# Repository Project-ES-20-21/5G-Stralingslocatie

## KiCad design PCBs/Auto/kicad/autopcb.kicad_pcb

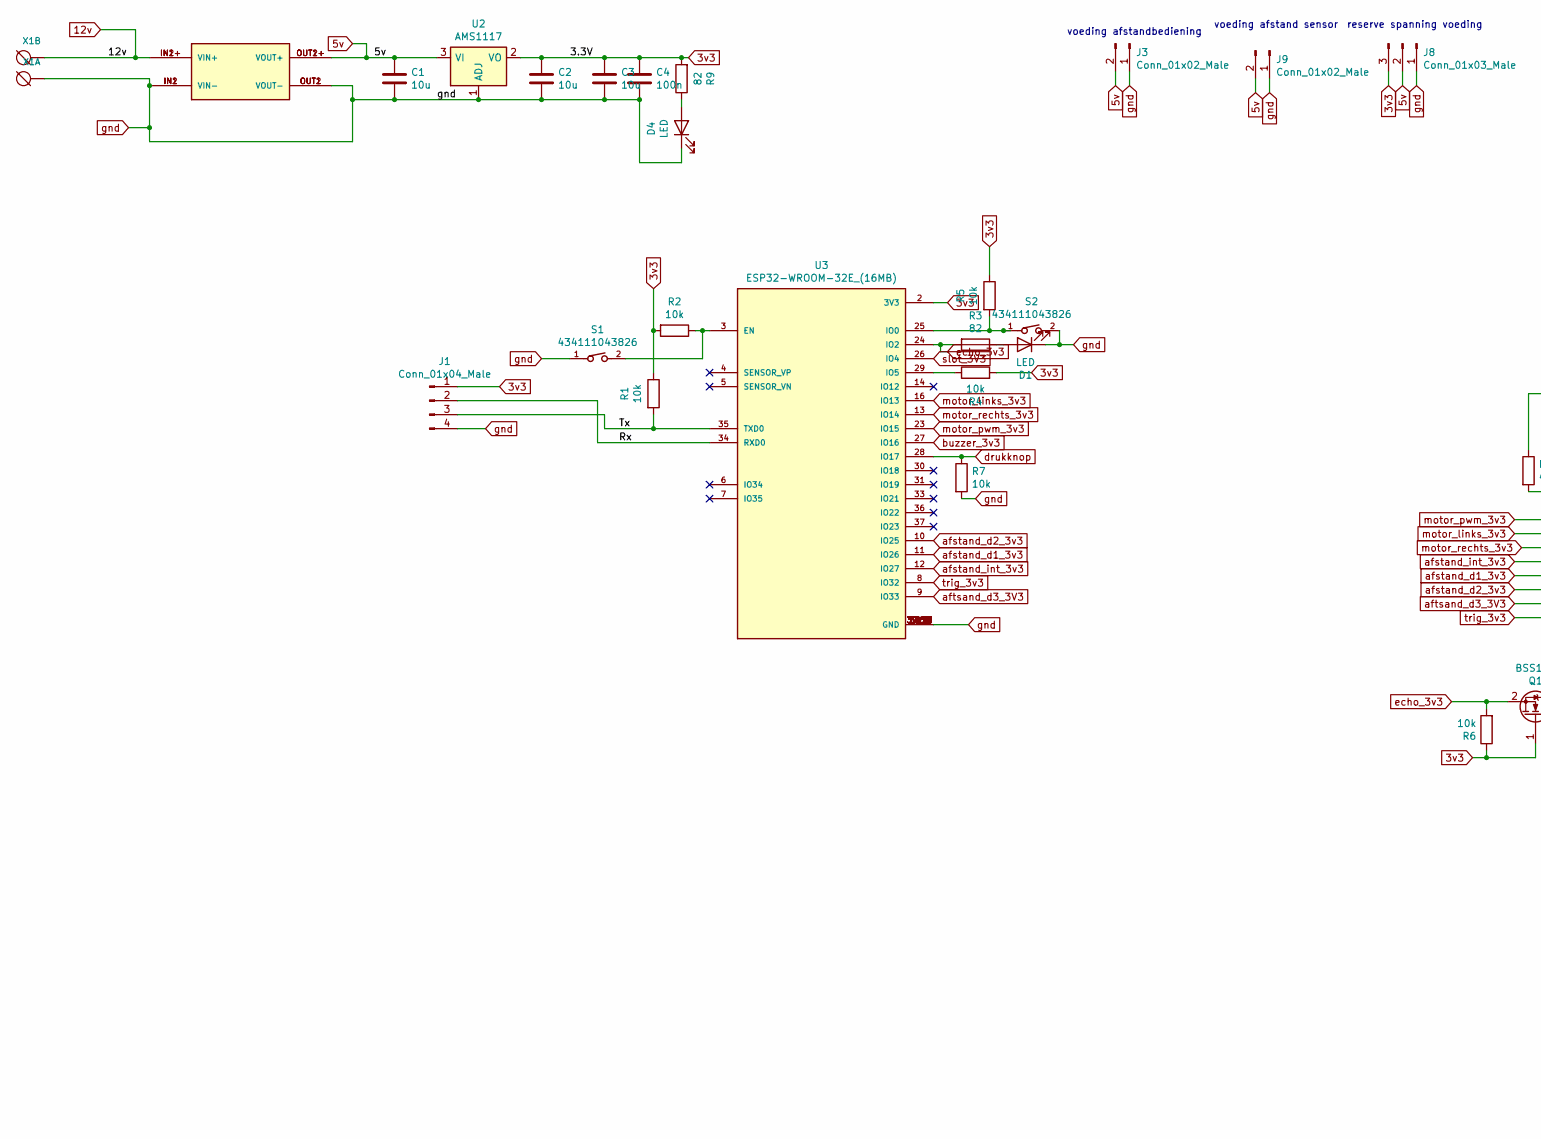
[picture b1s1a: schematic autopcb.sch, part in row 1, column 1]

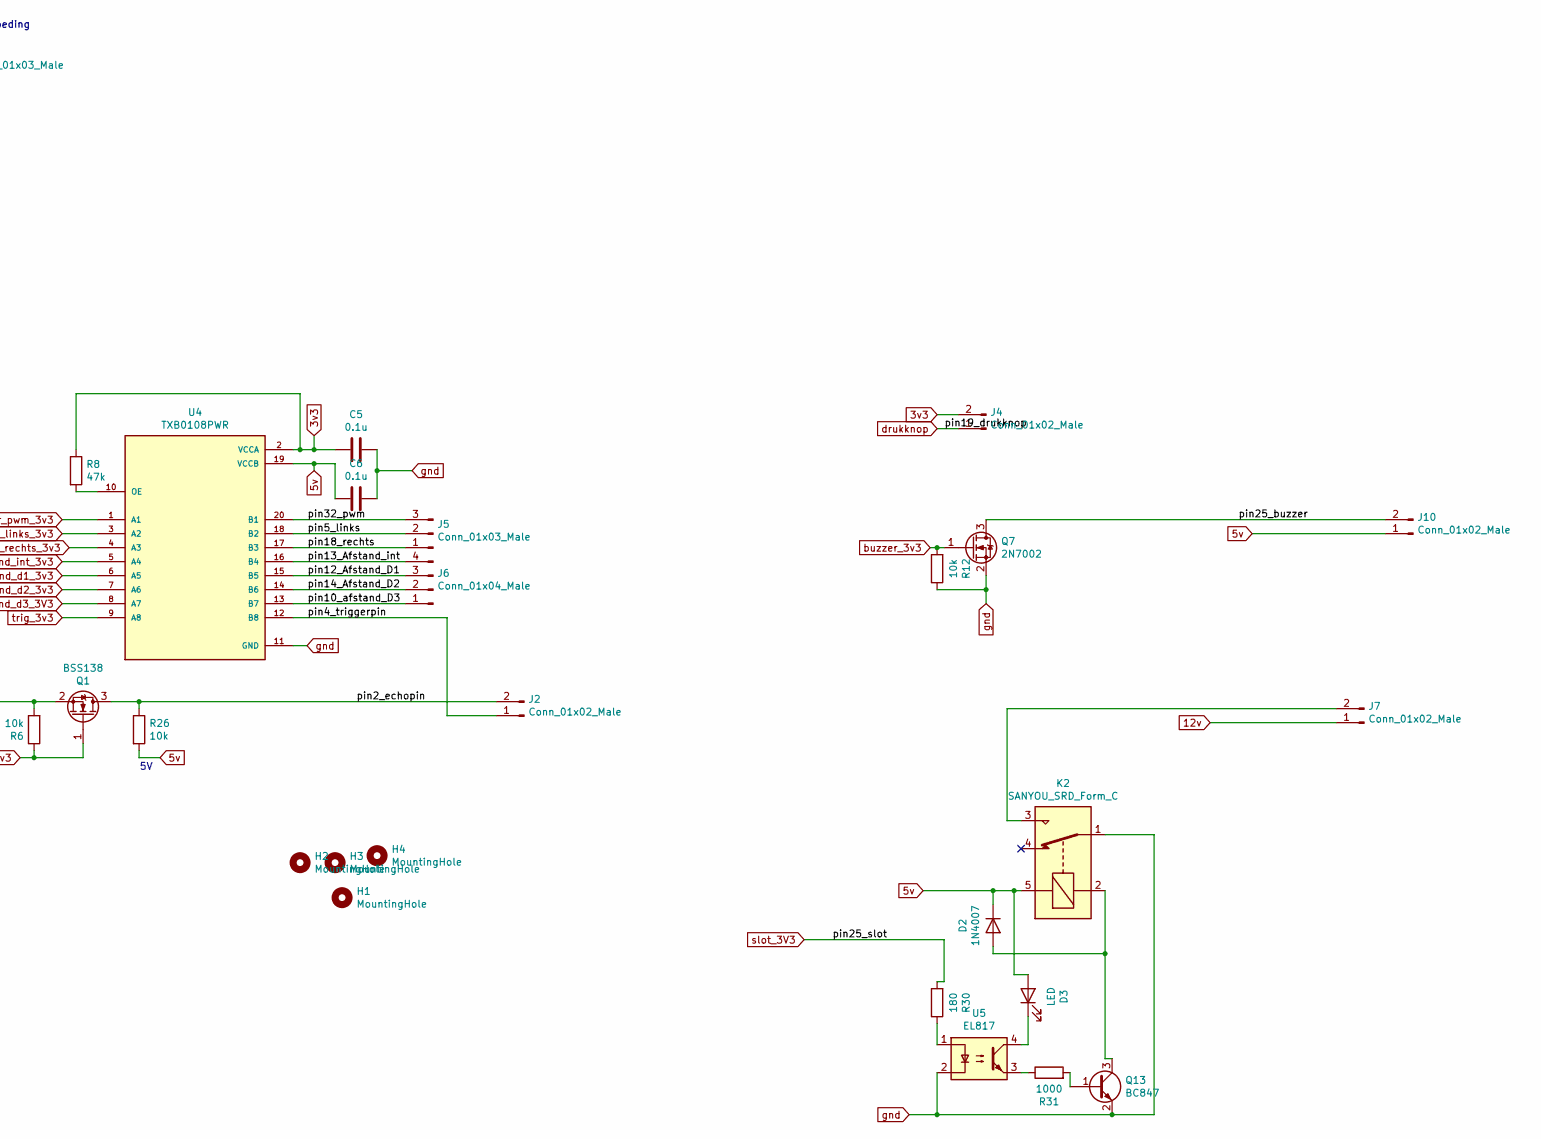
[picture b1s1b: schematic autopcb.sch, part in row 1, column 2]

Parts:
C1, C2, C3: 10u; C_0805_2012Metric_Pad1.18x1.45mm_HandSolder
C4: 100n; C_0805_2012Metric_Pad1.18x1.45mm_HandSolder
C5, C6: 0.1u; C_0805_2012Metric_Pad1.18x1.45mm_HandSolder
D1, D3, D4: LED; LED_0805_2012Metric_Pad1.15x1.40mm_HandSolder
D2: 1N4007; D_SMA_Handsoldering
H1, H2, H3, H4: MountingHole; MountingHole_4.5mm
J1, J6: Conn_01x04_Male; PinSocket_1x04_P2.54mm_Vertical
J2, J3, J4, J7, J9, J10: Conn_01x02_Male; PinSocket_1x02_P2.54mm_Vertical
J5, J8: Conn_01x03_Male; PinSocket_1x03_P2.54mm_Vertical
K2: SANYOU_SRD_Form_C; Relay_SPDT_SANYOU_SRD_Series_Form_C
Q1: BSS138; SOT-23
Q7: 2N7002; SOT-23
Q13: BC847; SOT-23
R1, R2, R4, R5, R6, R7, R12, R26: 10k; R_1206_3216Metric_Pad1.42x1.75mm_HandSolder
R3, R9: 82; R_1206_3216Metric_Pad1.42x1.75mm_HandSolder
R8: 47k; R_1206_3216Metric_Pad1.42x1.75mm_HandSolder
R30: 180; R_1206_3216Metric_Pad1.42x1.75mm_HandSolder
R31: 1000; R_1206_3216Metric_Pad1.42x1.75mm_HandSolder
S1, S2: 434111043826; PART-NUMBER 434111043826
U1: MP1584; buck
U2: AMS1117; SOT-223-3_TabPin2
U3: ESP32-WROOM-32E_(16MB); MODULE_ESP32-WROOM-32E_(16MB); PARTREV 1.1
U4: TXB0108PWR; SOP65P640X120-20N; PARTREV H
U5: EL817; DIP-4_W7.62mm
X1: DG3XX-02-3.5; degson-DG306-5.0-02P

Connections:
3v3: C2.1, C3.1, C4.1, C5.2, J1.1, J4.2, J8.3, Q1.1 (G), R1.1, R2.2, R4.2, R5.1, R6.1, R8.1, R9.2, U2.2 (VO), U3.2 (3V3), U4.2 (VCCA)
5v: C1.1, C6.1, D2.1 (K), D3.2 (A), J3.2, J8.2, J9.2, J10.1, K2.5, R26.2, U1.OUT1+ (VOUT+), U1.OUT2+ (VOUT+), U2.3 (VI), U4.19 (VCCB)
12v: J7.1, U1.IN1+ (VIN+), U1.IN2+ (VIN+), X1.2
/Rx: J1.2, U3.34 (RXD0)
/Tx: J1.3, R1.2, U3.35 (TXD0)
/pin2_echopin: J2.2, Q1.3 (D), R26.1
/pin4_triggerpin: J2.1, U4.12 (B8)
/pin5_links: J5.2, U4.18 (B2)
/pin10_afstand_D3: J6.1, U4.13 (B7)
/pin12_Afstand_D1: J6.3, U4.15 (B5)
/pin13_Afstand_int: J6.4, U4.16 (B4)
/pin14_Afstand_D2: J6.2, U4.14 (B6)
/pin18_rechts: J5.1, U4.17 (B3)
/pin25_buzzer: J10.2, Q7.3 (D)
/pin32_pwm: J5.3, U4.20 (B1)
unnamed: D1.2 (A), R3.1
unnamed: D2.2 (A), K2.2, Q13.3 (C)
unnamed: D3.1 (K), U5.4
unnamed: D4.2 (A), R9.1
unnamed: J7.2, K2.3
unnamed: Q13.1 (B), R31.2
unnamed: R2.1, S1.2, U3.3 (EN)
unnamed: R4.1, U3.29 (IO5)
unnamed: R5.2, S2.1, U3.25 (IO0)
unnamed: R8.2, U4.10 (OE)
unnamed: R30.1, U5.1
unnamed: R31.1, U5.3
afstand_d1_3v3: U3.11 (IO26), U4.6 (A5)
afstand_d2_3v3: U3.10 (IO25), U4.7 (A6)
afstand_int_3v3: U3.12 (IO27), U4.5 (A4)
aftsand_d3_3V3: U3.9 (IO33), U4.8 (A7)
buzzer_3v3: Q7.1 (G), R12.2, U3.27 (IO16)
drukknop: J4.1, R7.1, U3.28 (IO17)
echo_3v3: Q1.2 (S), R3.2, R6.2, U3.24 (IO2)
gnd: C1.2, C2.2, C3.2, C4.2, C5.1, C6.2, D1.1 (K), D4.1 (K), J1.4, J3.1, J8.1, J9.1, K2.1, Q7.2 (S), Q13.2 (E), R7.2, R12.1, S1.1, S2.2, U1.IN1 (VIN-), U1.IN2 (VIN-), U1.OUT1 (VOUT-), U1.OUT2 (VOUT-), U2.1 (ADJ), U3.1 (GND), U3.15 (GND), U3.38 (GND), U3.39_1 (GND), U3.39_2 (GND), U3.39_3 (GND), U3.39_4 (GND), U3.39_5 (GND), U3.39_6 (GND), U3.39_7 (GND), U3.39_8 (GND), U3.39_9 (GND), U3.39_10 (GND), U3.39_11 (GND), U3.39_12 (GND), U3.39_13 (GND), U3.39_14 (GND), U3.39_15 (GND), U3.39_16 (GND), U3.39_17 (GND), U3.39_18 (GND), U3.39_19 (GND), U3.39_20 (GND), U3.39_21 (GND), U4.11 (GND), U5.2, X1.1
motor_links_3v3: U3.16 (IO13), U4.3 (A2)
motor_pwm_3v3: U3.23 (IO15), U4.1 (A1)
motor_rechts_3v3: U3.13 (IO14), U4.4 (A3)
slot_3V3: R30.2, U3.26 (IO4)
trig_3v3: U3.8 (IO32), U4.9 (A8)

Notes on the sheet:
voeding afstand sensor
reserve spanning voeding
voeding afstandbediening

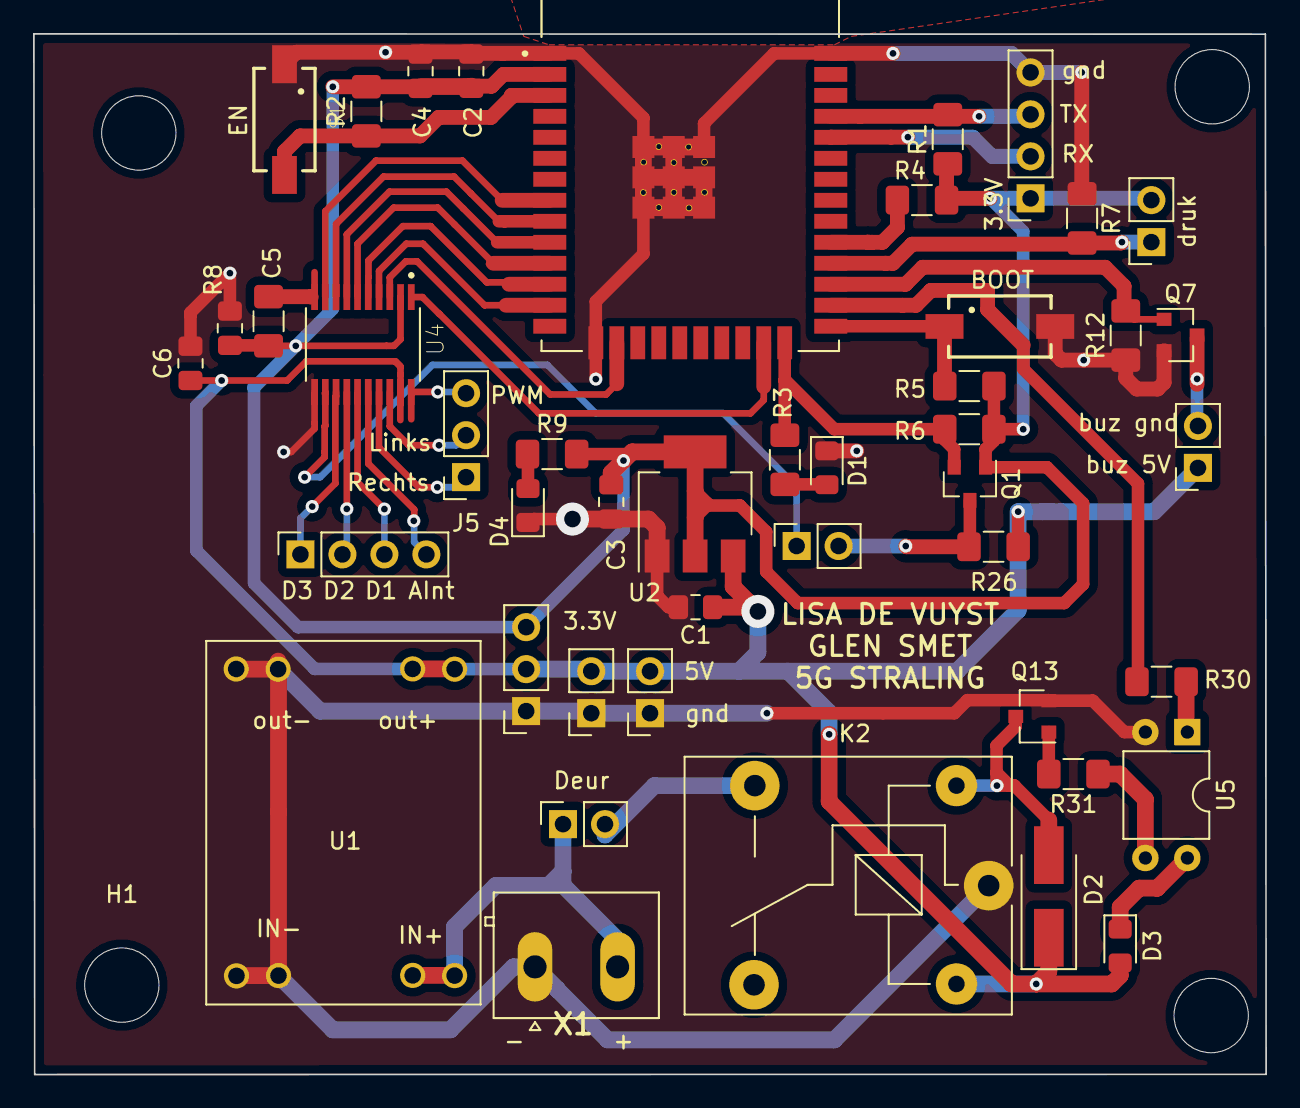
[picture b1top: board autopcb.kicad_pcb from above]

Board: 2 copper layers, 74.6 x 63.0 mm, 49 parts (0 on the bottom side), 40 nets.

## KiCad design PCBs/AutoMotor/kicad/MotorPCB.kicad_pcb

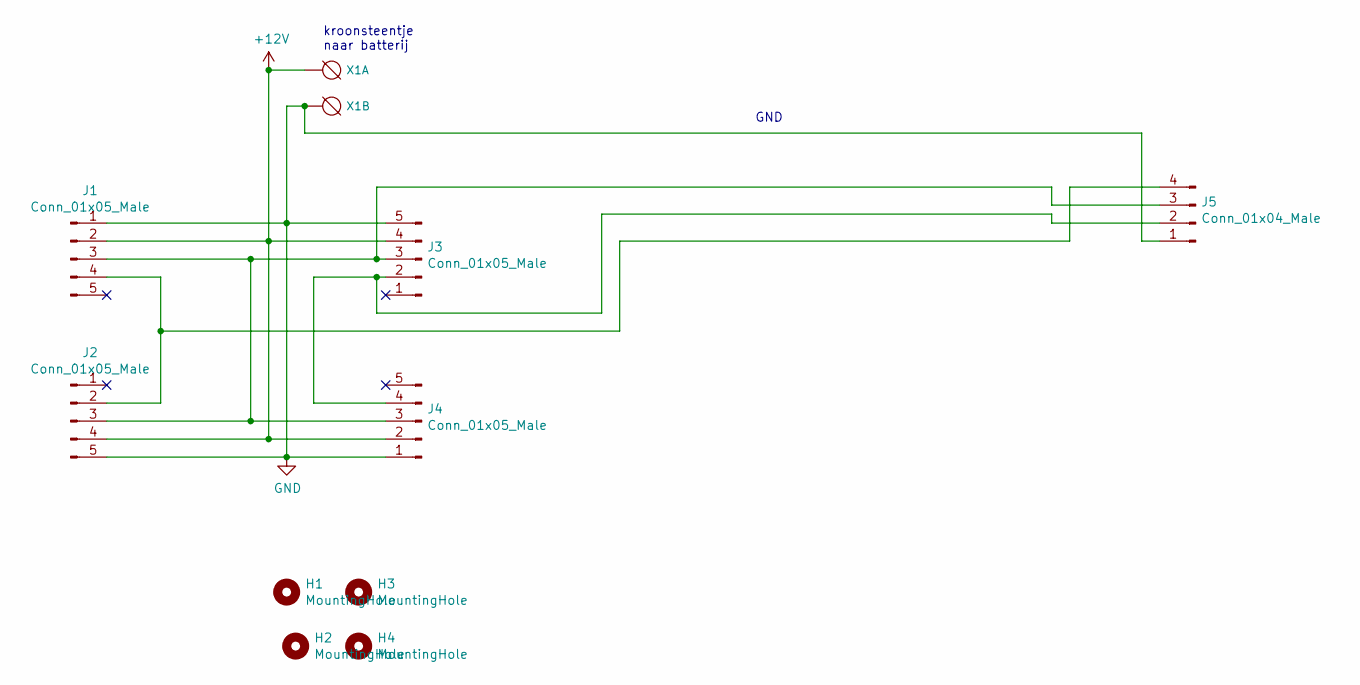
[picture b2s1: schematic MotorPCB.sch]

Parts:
H1, H2, H3, H4: MountingHole; MountingHole_4.5mm
J1, J2, J3, J4: Conn_01x05_Male; PinSocket_1x05_P2.54mm_Vertical
J5: Conn_01x04_Male; PinSocket_1x04_P2.54mm_Vertical
X1: DG3XX-02-5.0; degson-DG306-5.0-02P

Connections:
+12V: J1.2, J2.4, J3.4, J4.2, X1.1
GND: J1.1, J2.5, J3.5, J4.1, J5.1, X1.2
unnamed: J1.3, J2.3, J3.3, J4.3, J5.3
unnamed: J1.4, J2.2, J5.4
unnamed: J3.2, J4.4, J5.2

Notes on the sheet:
kroonsteentje naar batterij
GND

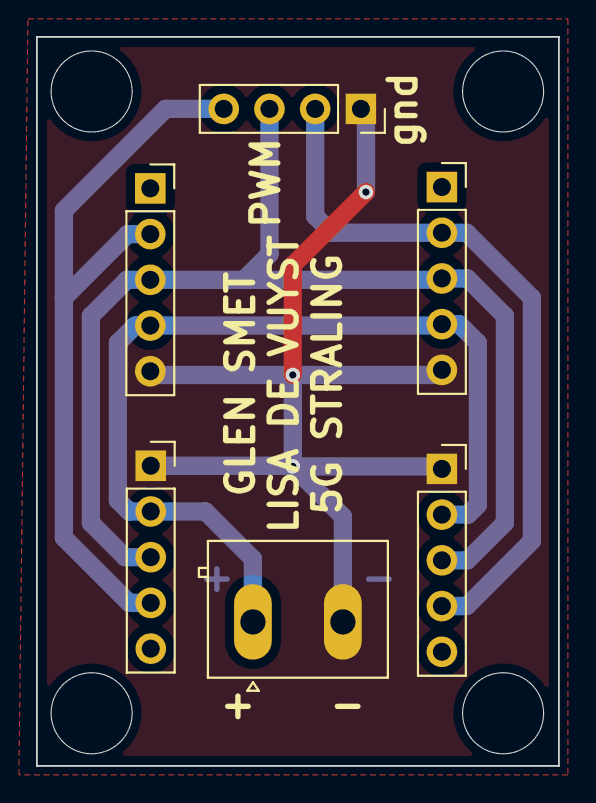
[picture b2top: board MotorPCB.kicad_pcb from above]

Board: 2 copper layers, 29.0 x 40.5 mm, 10 parts (0 on the bottom side), 5 nets.

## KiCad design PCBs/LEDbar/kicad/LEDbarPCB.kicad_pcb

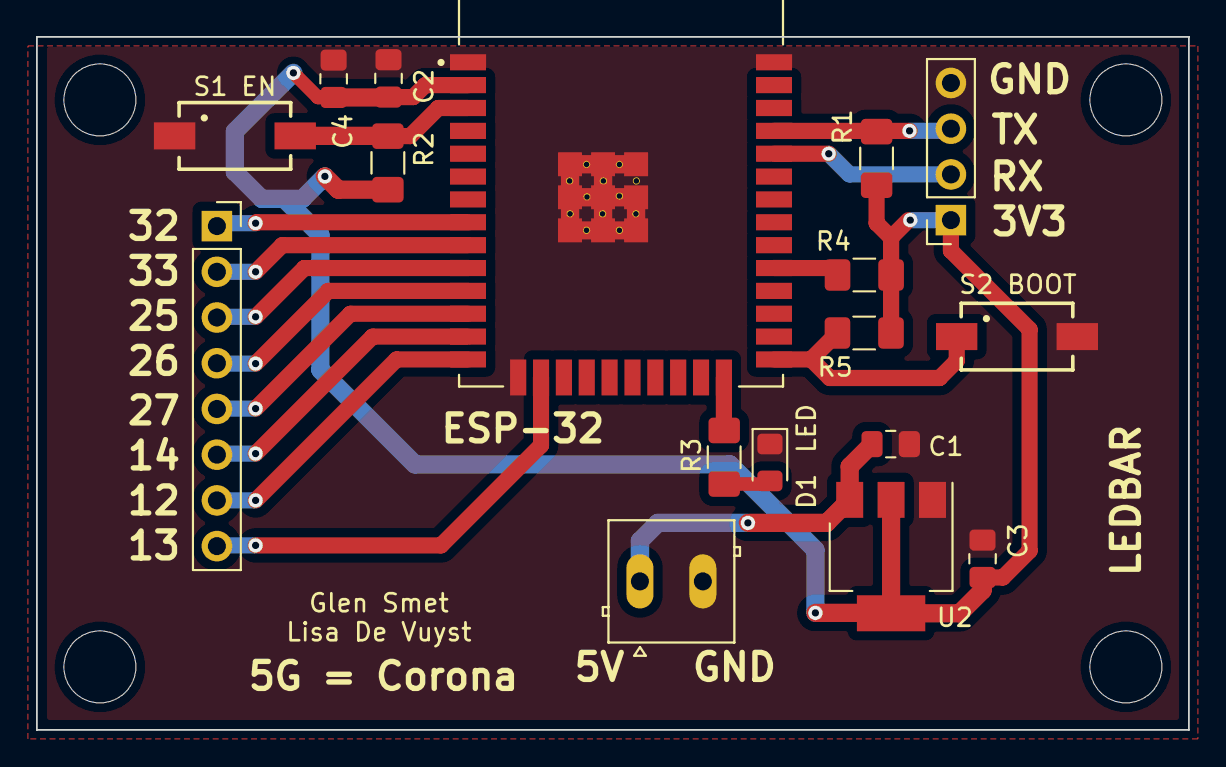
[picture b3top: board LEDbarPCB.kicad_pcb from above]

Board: 2 copper layers, 64.0 x 38.5 mm, 21 parts (0 on the bottom side), 18 nets.

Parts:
C1, C2, C3: 10u; C_0805_2012Metric_Pad1.18x1.45mm_HandSolder
C4: 100n; C_0805_2012Metric_Pad1.18x1.45mm_HandSolder
D1: LED; LED_0805_2012Metric_Pad1.15x1.40mm_HandSolder
H1, H3, H4: MountingHole; MountingHole_4mm
He: MountingHole; MountingHole_4mm
J1: Conn_01x04_Male; PinSocket_1x04_P2.54mm_Vertical
J2: Conn_01x08_Male; PinSocket_1x08_P2.54mm_Vertical
R1, R2, R4, R5: 10k; R_1206_3216Metric_Pad1.42x1.75mm_HandSolder
R3: 1k; R_1206_3216Metric_Pad1.42x1.75mm_HandSolder
S1 EN, S2 BOOT: 434111043826
U2: AMS1117; SOT-223-3_TabPin2
U3: ESP32-WROOM-32E_(16MB); MODULE_ESP32-WROOM-32E_(16MB)
X1: DG3XX-02-3.5; degson-DG350-3.5-02P

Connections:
3v3: C2.1, C3.1, C4.1, J1.1, R1.1, R2.2, R4.2, R5.1, U2.2, U3.2
5v: C1.1, U2.3, X1.1
/Rx: J1.2, U3.34
/Tx: J1.3, R1.2, U3.35
unnamed: D1.2, R3.1
unnamed: J2.1, U3.8
unnamed: J2.2, U3.9
unnamed: J2.3, U3.10
unnamed: J2.4, U3.11
unnamed: J2.5, U3.12
unnamed: J2.6, U3.13
unnamed: J2.7, U3.14
unnamed: J2.8, U3.16
unnamed: R2.1, S1 EN.2, U3.3
unnamed: R3.2, U3.24
unnamed: R4.1, U3.29
unnamed: R5.2, S2 BOOT.1, U3.25
gnd: C1.2, C2.2, C3.2, C4.2, D1.1, J1.4, S1 EN.1, S2 BOOT.2, U2.1, U3.1, U3.15, U3.38, U3.39_1, U3.39_2, U3.39_3, U3.39_4, U3.39_5, U3.39_6, U3.39_7, U3.39_8, U3.39_9, U3.39_20, X1.2

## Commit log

2021-05-12 Toevoegen Lasercut Files
2021-05-12 Toevoegen 3D-print Files
2021-05-12 Toevoegen Plattegrond
2021-05-12 Toevoegen Plattegrond - PDF
2021-05-12 Toevoegen PCB Stralingslocatie
2021-05-12 Toevoegen PCB LEDbar
2021-05-12 Toevoegen PCB Auto Motor
2021-05-12 Toevoegen PCB Auto
2021-05-12 Toevoegen Code ESP-32 Stralingslocatie
2021-05-15 Toevoegen Code ESP-32 LEDbar
2021-05-17 auto code
2021-05-18 Laatste Update Code main.cpp LEDbar
